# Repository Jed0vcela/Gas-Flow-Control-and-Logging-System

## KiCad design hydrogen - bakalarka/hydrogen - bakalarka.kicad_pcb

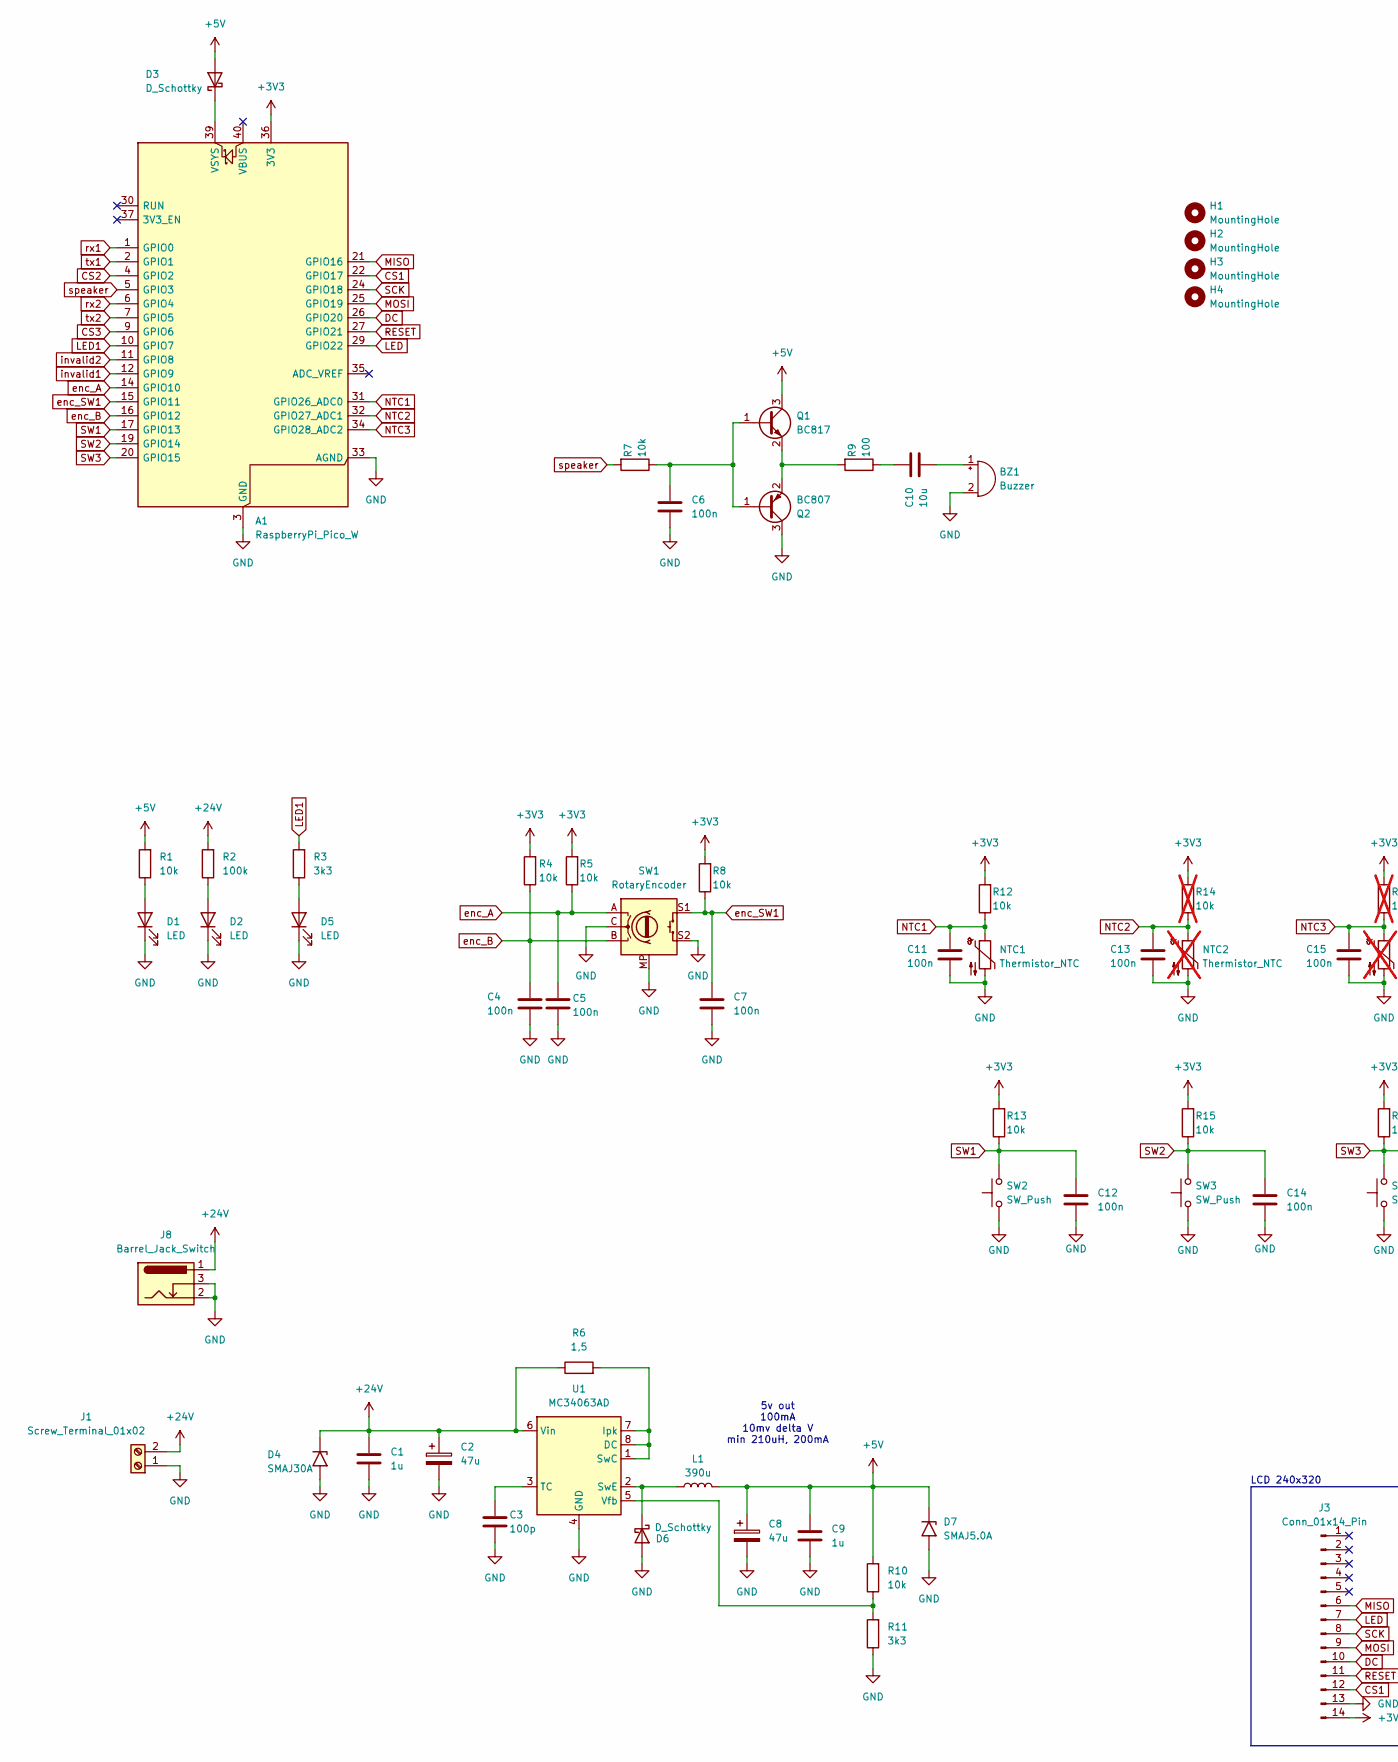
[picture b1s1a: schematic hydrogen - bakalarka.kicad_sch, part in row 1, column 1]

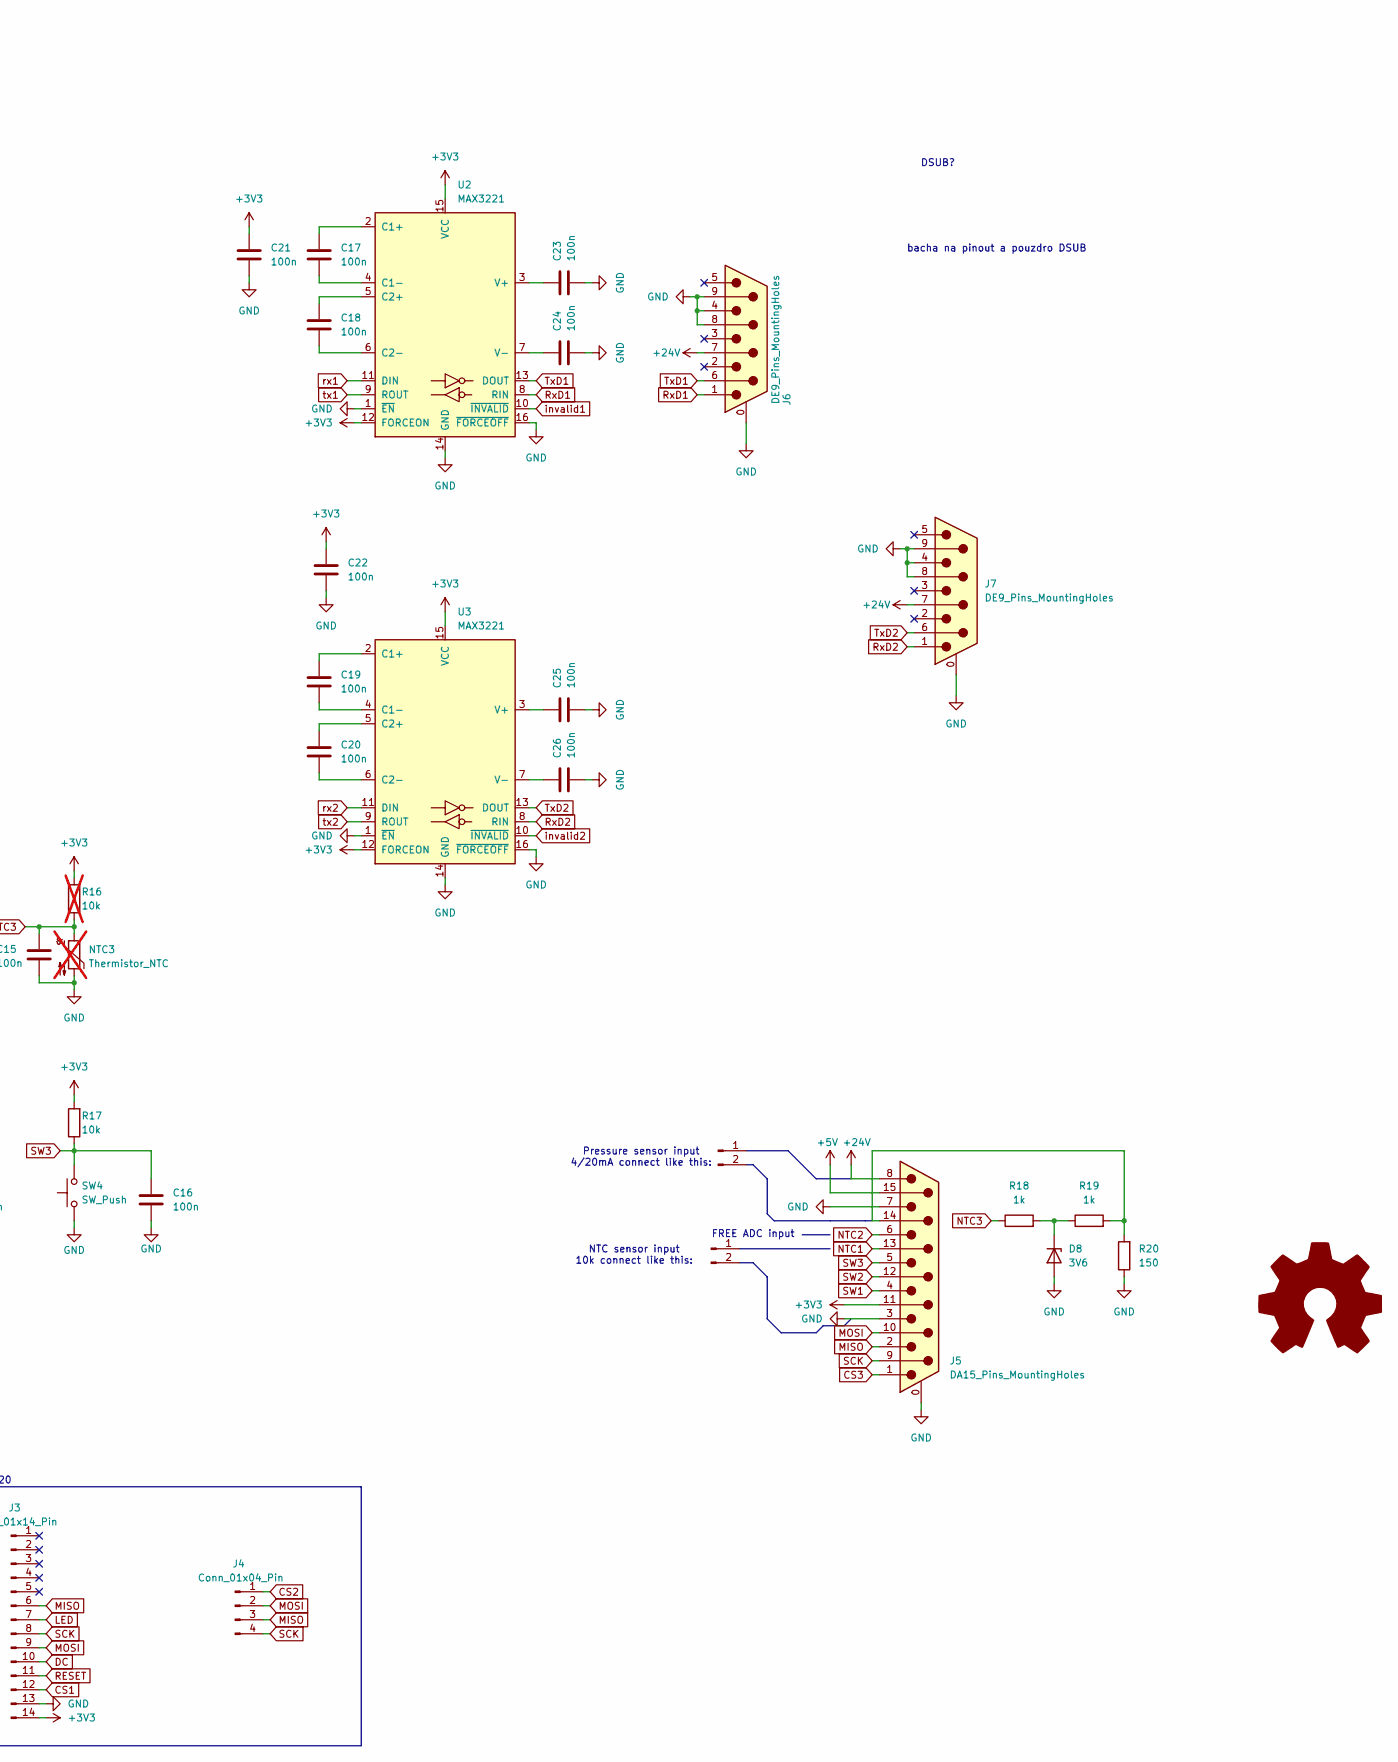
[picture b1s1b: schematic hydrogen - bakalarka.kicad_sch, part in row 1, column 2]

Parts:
A1: RaspberryPi_Pico_W; RaspberryPi_Pico_W_SMD_HandSolder
BZ1: Buzzer; Buzzer_15x7.5RM7.6
C1, C9: 1u; C_1206_3216Metric
C2, C8: 47u; CP_Radial_D6.3mm_P2.50mm
C3: 100p; C_0603_1608Metric
C4, C5, C6, C7, C11, C12, C13, C14, C15, C16, C17, C18, C19, C20, C21, C22, C23, C24, C25, C26: 100n; C_0603_1608Metric
C10: 10u; C_0603_1608Metric
D1, D2: LED; LED_0603_1608Metric
D3, D6: D_Schottky; D_SMA
D4: SMAJ30A; D_SMA
D5: LED; LED_D5.0mm
D7: SMAJ5.0A; D_SMA
D8: 3V6
H1, H2, H3, H4: MountingHole; MountingHole_3.2mm_M3_DIN965
J1: Screw_Terminal_01x02; TerminalBlock_RND_205-00287_1x02_P5.08mm_Horizontal
J2, J9: Conn_01x02_Pin
J3: Conn_01x14_Pin; PinHeader_1x14_P2.54mm_Vertical
J4: Conn_01x04_Pin; PinHeader_1x04_P2.54mm_Vertical
J5: DA15_Pins_MountingHoles; DSUB-15_Socket_Horizontal_P2.77x2.84mm_EdgePinOffset4.94mm_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
J6, J7: DE9_Pins_MountingHoles; DSUB-9_Pins_Horizontal_P2.77x2.84mm_EdgePinOffset4.94mm_Hou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
J8: Barrel_Jack_Switch; BarrelJack_GCT_DCJ200-10-A_Horizontal
L1: 390u; L_12x12mm_H8mm
NTC1: Thermistor_NTC; R_LDR_5.1x4.3mm_P3.4mm_Vertical
NTC2, NTC3: Thermistor_NTC; R_LDR_5.1x4.3mm_P3.4mm_Vertical; not fitted
Q1: BC817; SOT-23
Q2: BC807; SOT-23
R1, R4, R5, R7, R8, R10, R12, R13, R15, R17: 10k; R_0603_1608Metric
R2: 100k; R_0603_1608Metric
R3, R11: 3k3; R_0603_1608Metric
R6: 1,5; R_0603_1608Metric
R9: 100; R_0603_1608Metric
R14, R16: 10k; R_0603_1608Metric; not fitted
R18, R19: 1k
R20: 150
SW1: RotaryEncoder; RotaryEncoder_Alps_EC11E-Switch_Vertical_H20mm
SW2, SW3, SW4: SW_Push; SW_Cherry_MX_1.00u_PCB
U1: MC34063AD; SOIC-8_3.9x4.9mm_P1.27mm
U2, U3: MAX3221; TSSOP-16_4.4x5mm_P0.65mm

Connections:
+3V3: A1.36 (3V3), C21.1, C22.1, J3.14, J5.11 (P111), R4.2, R5.2, R8.2, R12.2, R13.2, R14.2, R15.2, R16.2, R17.2, U2.12 (FORCEON), U2.15 (VCC), U3.12 (FORCEON), U3.15 (VCC)
+5V: C8.1, C9.1, D3.2 (A), D7.1 (A1), J5.15, L1.2, Q1.3 (C), R1.2, R10.2
+24V: C1.1, C2.1, D4.1 (A1), J1.2, J5.8, J6.7, J7.7, J8.1, R2.2, R6.1, U1.6 (Vin)
CS1: A1.22 (GPIO17), J3.12
CS2: A1.4 (GPIO2), J4.1
CS3: A1.9 (GPIO6), J5.1
DC: A1.26 (GPIO20), J3.10
GND: A1.3 (GND), A1.8 (GND), A1.13 (GND), A1.18 (GND), A1.23 (GND), A1.28 (GND), A1.33 (AGND), A1.38 (GND), BZ1.2 (-), C1.2, C2.2, C3.2, C4.2, C5.2, C6.2, C7.2, C8.2, C9.2, C11.2, C12.2, C13.2, C14.2, C15.2, C16.2, C21.2, C22.2, C23.2, C24.2, C25.2, C26.2, D1.1 (K), D2.1 (K), D4.2 (A2), D5.1 (K), D6.2 (A), D7.2 (A2), D8.2 (A), J1.1, J3.13, J5.0 (PAD), J5.3, J5.7, J6.0 (PAD), J6.4, J6.8, J6.9, J7.0 (PAD), J7.4, J7.8, J7.9, J8.2, J8.3, NTC1.2, NTC2.2, NTC3.2, Q2.3 (C), R11.1, R20.1, SW1.C, SW1.MP, SW1.S2, SW2.1, SW3.1, SW4.1, U1.4 (GND), U2.1 (~EN), U2.14 (GND), U2.16 (~FORCEOFF), U3.1 (~EN), U3.14 (GND), U3.16 (~FORCEOFF)
LED: A1.29 (GPIO22), J3.7
LED1: A1.10 (GPIO7), R3.2
MISO: A1.21 (GPIO16), J3.6, J4.3, J5.2
MOSI: A1.25 (GPIO19), J3.9, J4.2, J5.10
NTC1: A1.31 (GPIO26_ADC0), C11.1, J5.13, NTC1.1, R12.1
NTC2: A1.32 (GPIO27_ADC1), C13.1, J5.6, NTC2.1, R14.1
NTC3: A1.34 (GPIO28_ADC2), C15.1, J5.14, NTC3.1, R16.1, R18.1, R19.2, R20.2
unnamed: A1.39 (VSYS), D3.1 (K)
unnamed: BZ1.1 (+), C10.2
unnamed: C10.1, R9.1
unnamed: D1.2 (A), R1.1
unnamed: D2.2 (A), R2.1
unnamed: D5.2 (A), R3.1
unnamed: D6.1 (K), L1.1, U1.2 (SwE)
unnamed: D8.1 (K), R18.2, R19.1
unnamed: C6.1, Q1.1 (B), Q2.1 (B), R7.1
unnamed: Q1.2 (E), Q2.2 (E), R9.2
unnamed: R6.2, U1.1 (SwC), U1.7 (Ipk), U1.8 (DC)
unnamed: C3.1, U1.3 (TC)
unnamed: R10.1, R11.2, U1.5 (Vfb)
unnamed: C17.2, U2.2 (C1+)
unnamed: C17.1, U2.4 (C1-)
unnamed: C18.2, U2.5 (C2+)
unnamed: C18.1, U2.6 (C2-)
unnamed: C23.1, U2.3 (V+)
unnamed: C24.1, U2.7 (V-)
unnamed: C19.2, U3.2 (C1+)
unnamed: C19.1, U3.4 (C1-)
unnamed: C20.2, U3.5 (C2+)
unnamed: C20.1, U3.6 (C2-)
unnamed: C25.1, U3.3 (V+)
unnamed: C26.1, U3.7 (V-)
RESET: A1.27 (GPIO21), J3.11
RxD1: J6.1, U2.8 (RIN)
RxD2: J7.1, U3.8 (RIN)
SCK: A1.24 (GPIO18), J3.8, J4.4, J5.9
SW1: A1.17 (GPIO13), C12.1, J5.4, R13.1, SW2.2
SW2: A1.19 (GPIO14), C14.1, J5.12, R15.1, SW3.2
SW3: A1.20 (GPIO15), C16.1, J5.5, R17.1, SW4.2
TxD1: J6.6, U2.13 (DOUT)
TxD2: J7.6, U3.13 (DOUT)
enc_A: A1.14 (GPIO10), C5.1, R5.1, SW1.A
enc_B: A1.16 (GPIO12), C4.1, R4.1, SW1.B
enc_SW1: A1.15 (GPIO11), C7.1, R8.1, SW1.S1
invalid1: A1.12 (GPIO9), U2.10 (~INVALID)
invalid2: A1.11 (GPIO8), U3.10 (~INVALID)
rx1: A1.1 (GPIO0), U2.11 (DIN)
rx2: A1.6 (GPIO4), U3.11 (DIN)
speaker: A1.5 (GPIO3), R7.2
tx1: A1.2 (GPIO1), U2.9 (ROUT)
tx2: A1.7 (GPIO5), U3.9 (ROUT)

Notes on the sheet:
LCD 240x320
FREE ADC input
5v out 100mA 10mv delta V min 210uH, 200mA
Pressure sensor input 4/20mA connect like this:
NTC sensor input 10k connect like this:
bacha na pinout a pouzdro DSUB
DSUB?

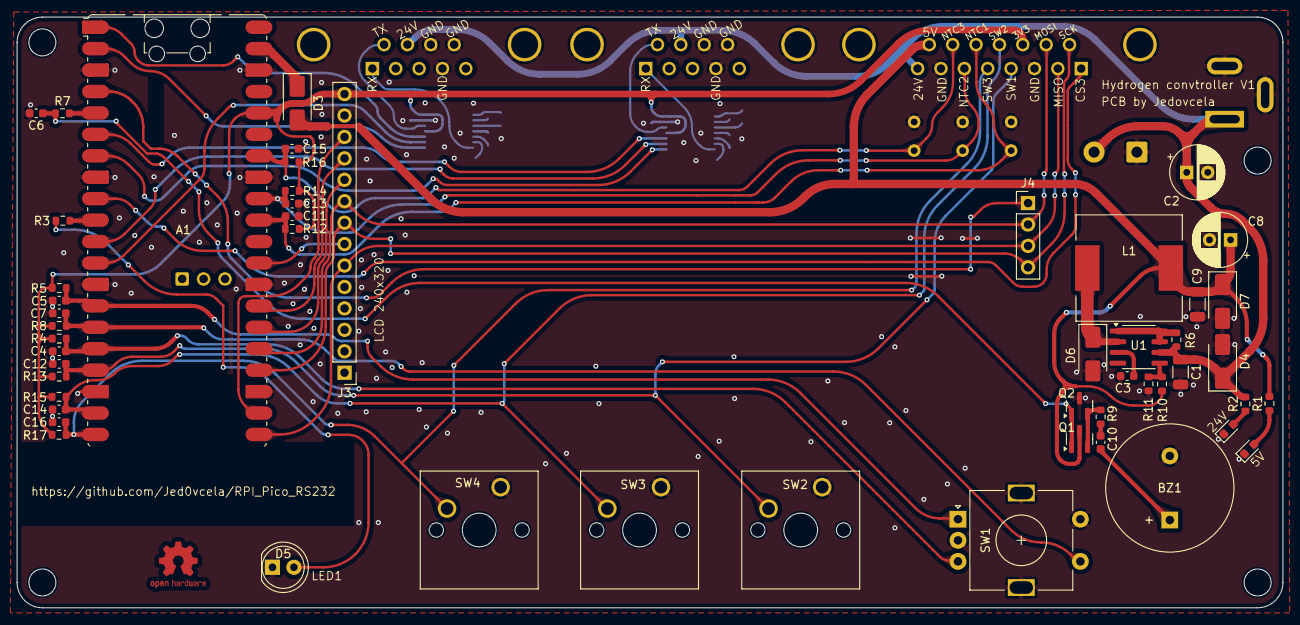
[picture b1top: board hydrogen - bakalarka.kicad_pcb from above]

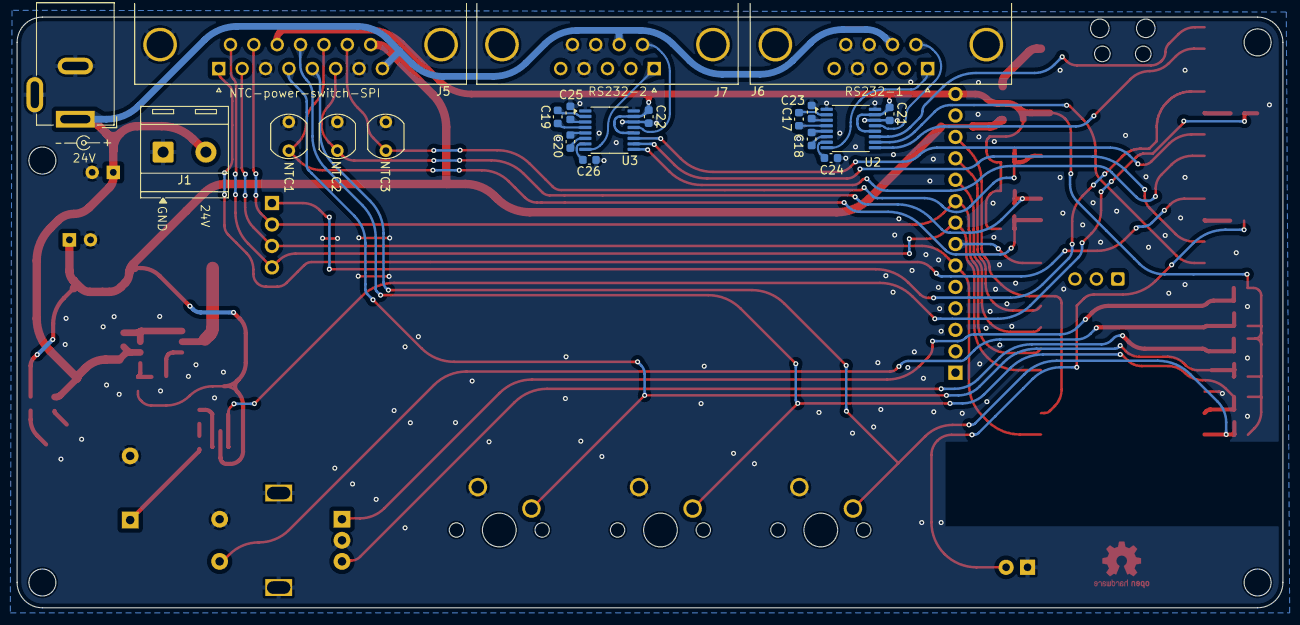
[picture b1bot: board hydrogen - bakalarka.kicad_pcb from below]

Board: 2 copper layers, 150.0 x 70.0 mm, 76 parts (20 on the bottom side), 58 nets.

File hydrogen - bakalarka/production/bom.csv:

Designator,Footprint,Quantity,Value,LCSC Part #
A1,RaspberryPi_Pico_W_SMD_HandSolder,1,RaspberryPi_Pico_W,
BZ1,Buzzer_15x7.5RM7.6,1,Buzzer,
"C1, C9",1206,2,1u,
C10,0603,1,10u,
"C11, C12, C13, C14, C15, C16, C17, C18, C19, C20, C21, C22, C23, C24, C25, C26, C4, C5, C6, C7",0603,20,100n,
"C2, C8",CP_Radial_D6.3mm_P2.50mm,2,47u,
C3,0603,1,100p,
"D1, D2",0603,2,LED,
"D3, D6",D_SMA,2,D_Schottky,
D4,D_SMA,1,SMAJ30A,
D5,LED_D5.0mm,1,LED,
D7,D_SMA,1,SMAJ5.0A,
J1,TerminalBlock_RND_205-00287_1x02_P5.08mm_Horizontal,1,Screw_Terminal_01x02,
J3,PinHeader_1x14_P2.54mm_Vertical,1,Conn_01x14_Pin,
J4,PinHeader_1x04_P2.54mm_Vertical,1,Conn_01x04_Pin,
J5,DSUB-15_Socket_Horizontal_P2.77x2.84mm_EdgePinOffset4.94mm_Housed_MountingHolesOffset4.94mm,1,DA15_Pins_MountingHoles,
"J6, J7",DSUB-9_Pins_Horizontal_P2.77x2.84mm_EdgePinOffset4.94mm_Housed_MountingHolesOffset4.94mm,2,DE9_Pins_MountingHoles,
J8,BarrelJack_GCT_DCJ200-10-A_Horizontal,1,Barrel_Jack_Switch,
L1,L_12x12mm_H8mm,1,390u,
"NTC1, NTC2, NTC3",R_LDR_5.1x4.3mm_P3.4mm_Vertical,3,Thermistor_NTC,
Q1,SOT-23,1,BC817,
Q2,SOT-23,1,BC807,
"R1, R12, R13, R14, R15, R16, R17, R4, R5, R7, R8",0603,11,10k,
R10,0603,1,3k,
"R11, R3",0603,2,1k,
R2,0603,1,100k,
R6,0603,1,"1,5",
R9,0603,1,100,
SW1,RotaryEncoder_Alps_EC11E-Switch_Vertical_H20mm,1,RotaryEncoder,
"SW2, SW3, SW4",SW_Cherry_MX_1.00u_PCB,3,SW_Push,
U1,SOIC-8_3.9x4.9mm_P1.27mm,1,MC34063AD,
"U2, U3",TSSOP-16_4.4x5mm_P0.65mm,2,MAX3221,

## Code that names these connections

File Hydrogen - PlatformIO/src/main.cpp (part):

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#define sw_1        15
#define sw_2        14
#define sw_3        13
#define ENC_A       10
#define ENC_B       12
#define ENC_BTN     11

/* ---- ADC ----------------------------------------------------------------- */
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static volatile int32_t enc_delta = 0;
static void encoder_irq(uint gpio, uint32_t events) {
    (void)gpio; (void)events;
    bool a = gpio_get(ENC_A), b = gpio_get(ENC_B);
    if (a == b) enc_delta--; else enc_delta++;
}
static int32_t enc_read_clear(void) {
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    for (size_t i = 0; i < 4; i++) {
        gpio_init(btns[i]); gpio_set_dir(btns[i], GPIO_IN); gpio_pull_up(btns[i]);
    }
    gpio_init(ENC_A); gpio_set_dir(ENC_A, GPIO_IN); gpio_pull_up(ENC_A);
    gpio_init(ENC_B); gpio_set_dir(ENC_B, GPIO_IN); gpio_pull_up(ENC_B);
    gpio_set_irq_enabled_with_callback(ENC_A,
        GPIO_IRQ_EDGE_RISE | GPIO_IRQ_EDGE_FALL, true, encoder_irq);
    gpio_init(LED_ONBOARD); gpio_set_dir(LED_ONBOARD, GPIO_OUT);
    gpio_init(LED_KA);      gpio_set_dir(LED_KA,      GPIO_OUT);
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    uint64_t all3_since = 0;
    bool     all3_armed = false;

    int32_t ntc1 = -9999, ntc2 = -9999, press = 0;
    int32_t ntc2_mv = 0;
    uint64_t alarm_beep_us = 0;
    uint64_t fps_ref = now_us; uint32_t fps_cnt = 0; uint16_t fps = 0;
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
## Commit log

2026-06-02 initial Kicad and 3D files upload
    KiCad files and 3D SolidWorks files upload
2026-06-02 rename
    dir rename
2026-06-02 rename
2026-06-02 upload compiled firmware
2026-06-02 upload
    Python control script for controlling from PC. With Matplotlib GUI
